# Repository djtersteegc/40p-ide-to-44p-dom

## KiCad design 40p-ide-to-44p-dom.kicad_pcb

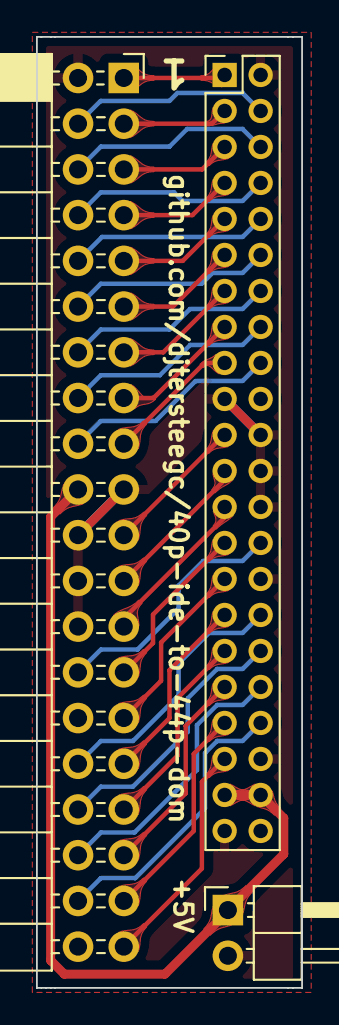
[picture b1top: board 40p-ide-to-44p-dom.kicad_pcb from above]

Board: 2 copper layers, 14.7 x 52.8 mm, 3 parts (0 on the bottom side), 34 nets.

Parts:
J1: IDE 44 pin; PinHeader_2x22_P2.00mm_Vertical
J2: IDE 40 pin; PinSocket_2x20_P2.54mm_Horizontal
J3: 5V Power; PinHeader_1x02_P2.54mm_Horizontal

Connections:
+5V: J1.41, J1.42, J2.20, J3.1
GND: J1.2, J1.19, J1.22, J1.24, J1.26, J1.30, J1.40, J1.43, J2.2, J2.19, J2.22, J2.24, J2.26, J2.30, J2.40, J3.2
unnamed: J1.1, J2.1
unnamed: J1.3, J2.3
unnamed: J1.4, J2.4
unnamed: J1.5, J2.5
unnamed: J1.6, J2.6
unnamed: J1.7, J2.7
unnamed: J1.8, J2.8
unnamed: J1.9, J2.9
unnamed: J1.10, J2.10
unnamed: J1.11, J2.11
unnamed: J1.12, J2.12
unnamed: J1.13, J2.13
unnamed: J1.14, J2.14
unnamed: J1.15, J2.15
unnamed: J1.16, J2.16
unnamed: J1.17, J2.17
unnamed: J1.18, J2.18
unnamed: J1.21, J2.21
unnamed: J1.23, J2.23
unnamed: J1.25, J2.25
unnamed: J1.27, J2.27
unnamed: J1.28, J2.28
unnamed: J1.29, J2.29
unnamed: J1.31, J2.31
unnamed: J1.32, J2.32
unnamed: J1.33, J2.33
unnamed: J1.34, J2.34
unnamed: J1.35, J2.35
unnamed: J1.36, J2.36
unnamed: J1.37, J2.37
unnamed: J1.38, J2.38
unnamed: J1.39, J2.39
